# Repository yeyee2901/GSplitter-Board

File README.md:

# GSplitter Board

### Front Layer
Solid Copper pour  

### Bottom Layer
Signals

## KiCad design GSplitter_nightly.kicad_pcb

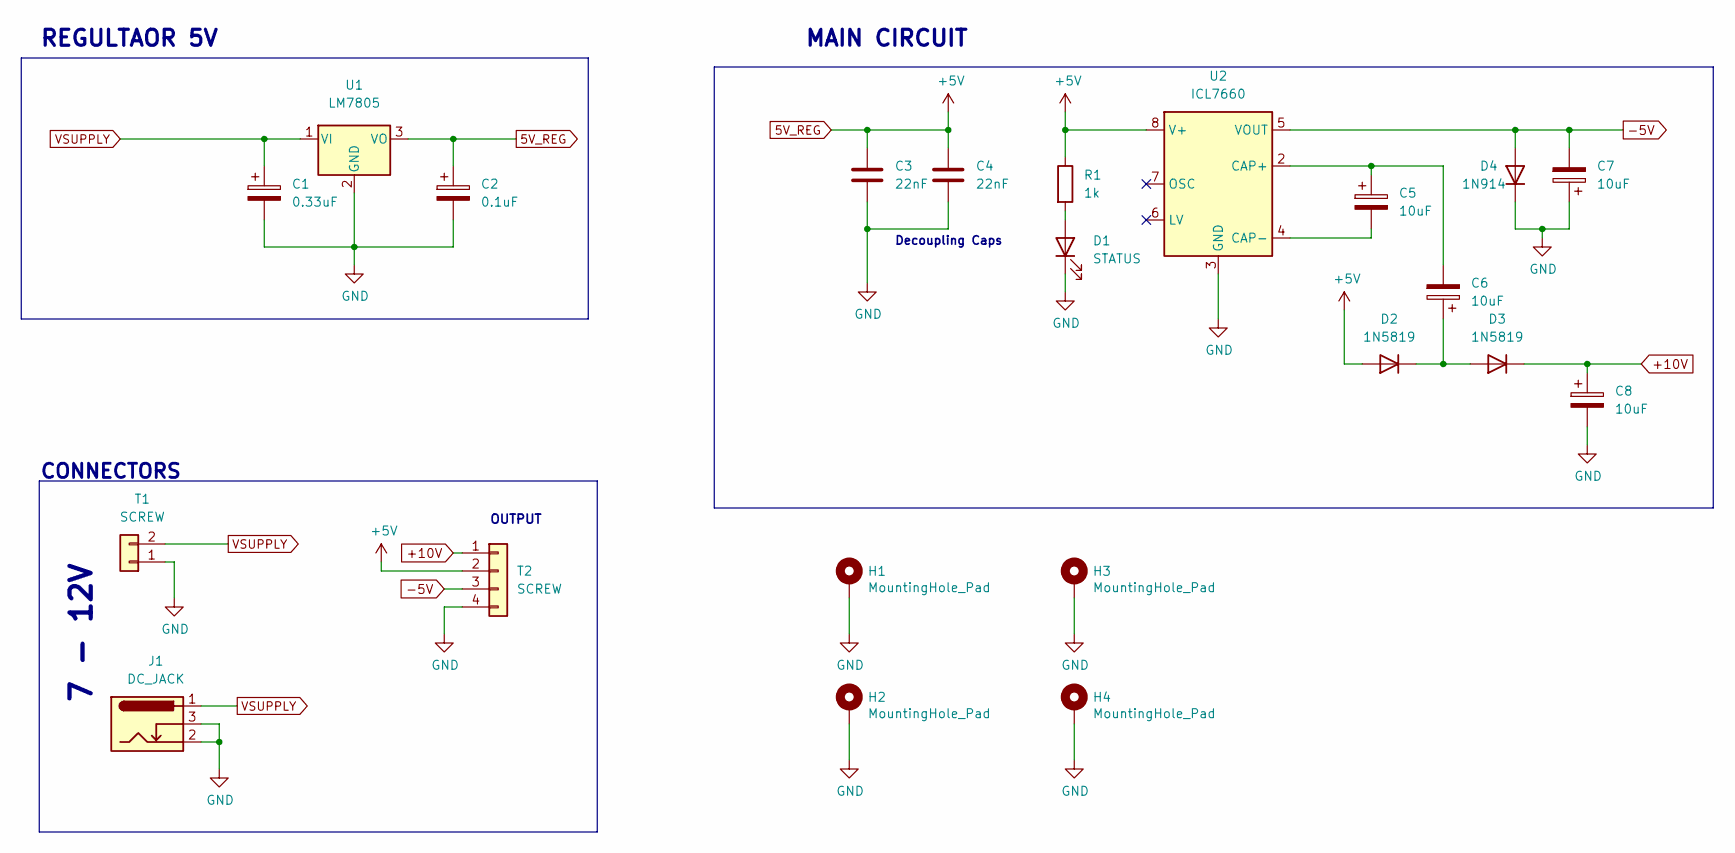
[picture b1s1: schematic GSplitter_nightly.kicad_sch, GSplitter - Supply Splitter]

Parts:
C1: 0.33uF; CP_Radial_D4.0mm_P2.00mm
C2: 0.1uF; CP_Radial_D4.0mm_P2.00mm
C3, C4: 22nF; C_Disc_D3.0mm_W2.0mm_P2.50mm
C5, C6, C7, C8: 10uF; CP_Radial_D5.0mm_P2.50mm
D1: STATUS; LED_D5.0mm
D2, D3: 1N5819; D_DO-41_SOD81_P12.70mm_Horizontal
D4: 1N914; D_DO-41_SOD81_P12.70mm_Horizontal
H1, H2, H3, H4: MountingHole_Pad; MountingHole_3.2mm_M3_Pad
J1: DC_JACK; BarrelJack_Horizontal
R1: 1k; R_Axial_DIN0207_L6.3mm_D2.5mm_P10.16mm_Horizontal
T1: SCREW; TerminalBlock_Phoenix_MKDS-1,5-2_1x02_P5.00mm_Horizontal
T2: SCREW; TerminalBlock_Phoenix_MKDS-1,5-4-5.08_1x04_P5.08mm_Horizont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
U1: LM7805; TO-220-3_Horizontal_TabDown
U2: ICL7660; DIP-8_W7.62mm

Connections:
5V_REG: C2.1, C3.1, C4.1, D2.2 (A), R1.1, T2.2, U1.3 (VO), U2.8 (V+)
+10V: C8.1, D3.1 (K), T2.1
-5V: C7.2, D4.2 (A), T2.3, U2.5 (VOUT)
GND: C1.2, C2.2, C3.2, C4.2, C7.1, C8.2, D1.1 (K), D4.1 (K), H1.1, H2.1, H3.1, H4.1, J1.2, J1.3, T1.1, T2.4, U1.2 (GND), U2.3 (GND)
unnamed: C5.1, C6.2, U2.2 (CAP+)
unnamed: C5.2, U2.4 (CAP-)
unnamed: C6.1, D2.1 (K), D3.2 (A)
unnamed: D1.2 (A), R1.2
VSUPPLY: C1.1, J1.1, T1.2, U1.1 (VI)

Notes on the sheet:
REGULTAOR 5V
CONNECTORS
7 - 12V
OUTPUT
MAIN CIRCUIT
Decoupling Caps

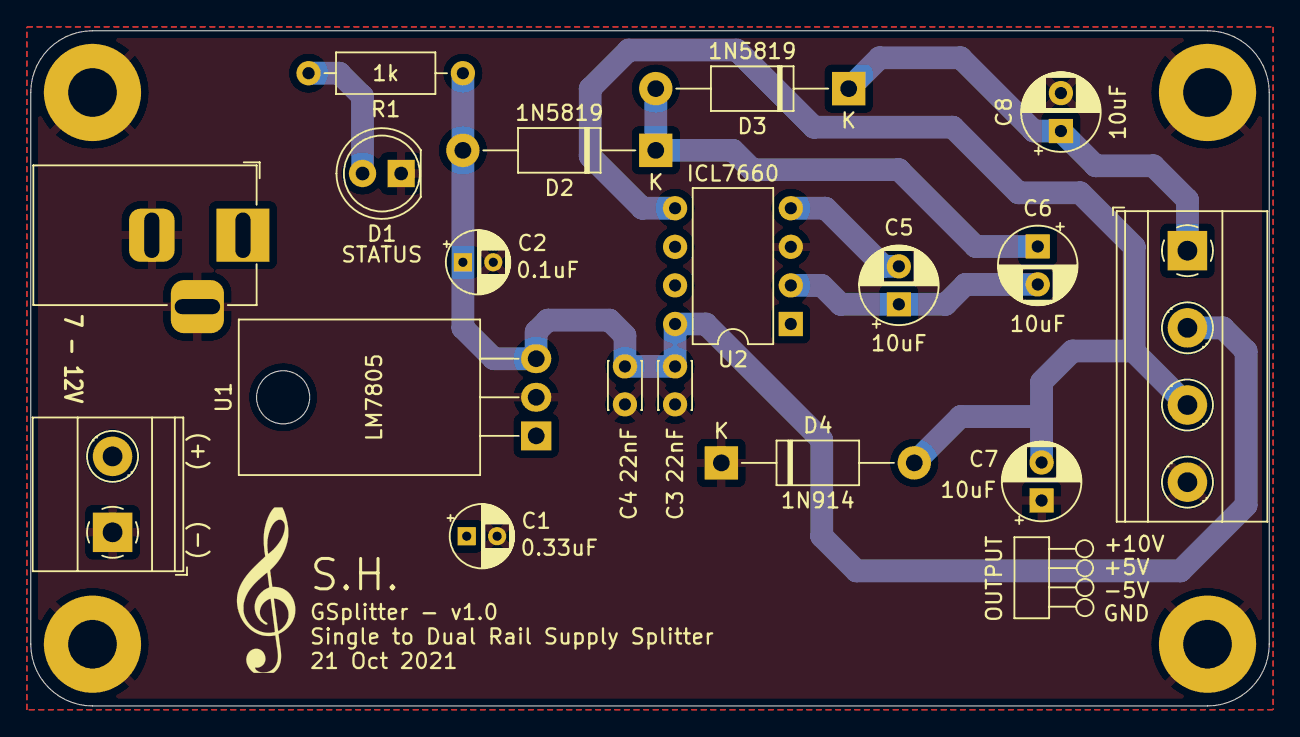
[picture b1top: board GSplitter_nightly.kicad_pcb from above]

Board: 2 copper layers, 81.5 x 44.4 mm, 22 parts (0 on the bottom side), 9 nets.

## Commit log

2021-11-01 ADD: README.md
2021-11-01 ADD Images
2021-11-03 Change to nightly KiCAD
2021-11-03 ADD: Git ignore
2021-11-04 Smooth out the VSUPPLY net fill zone
